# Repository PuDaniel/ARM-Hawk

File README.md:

The ARM-Hawk project consists of a custom designed radio controlled airplane equipped with a scratch built flight computer running custom software. The goal of the project is to develop a system to greatly enhance the flight characteristics of the airplane, as well as to protect its flight envelope.
This repository includes the following parts of the project:

- [ARM_Hawk.pdf](ARM_Hawk.pdf) This file contains a complete description of the project, including the derivation of a flight model and simulation framework, sensor calibration and state estimation algorithms, and the control laws for lateral stability augmentation and stall protection
- [Air_Data_Sensor_Unit](Air_Data_Sensor_Unit) This directory contains information for building and calibrating the custom developed Air Data Probe
- [Airframe](Airframe) This directory contains some information about the airplane used
- [Electronics](Electronics) This directory contains plans for some electronic circuits (RPM sensor, servo switch)
- [Flight_Computer](Flight_Computer) This directory contains the C++ code for the flight software
- [IMU](IMU) This directory contains information for building and calibrating the custom developed Inertial Measurement Unit, as well as a model of the state estimation algorithm

Visit the project's YouTube channel to see some videos of the system in action:
[https://m.youtube.com/channel/UCTHfZXQw1zonnjaXaEWrNzA](https://m.youtube.com/channel/UCTHfZXQw1zonnjaXaEWrNzA)

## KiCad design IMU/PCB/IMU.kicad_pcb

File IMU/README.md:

# IMU

This directory contains all plans to build and calibrate the ARM-Hawk custom designed IMU. It consits of an *NXP FXAS21002* gyroscope and an *NXP FXOS8700* accelerometer/magnetometer. A CNC-machined baseplate provides an exact reference for calibration and mounting in the plane. A 3D-printed case protects the sensor ICs form high-current cables (magnetic fields).

- [Calibration_accelerometer](Calibration_accelerometer) contains a Matlab script to calibrate the accelerometer (a sample dataset and result is also included)
- [Calibration_gyro](Calibration_gyro) contains a Matlab script to calibrate the gyroscope (a sample dataset and result is also included)
- [Calibration_magnetometer](Calibration_magnetometer) contains two Matlab scripts to calibrate the magnetometer for the static case and the dynamic case with the motor running (a sample dataset and result is also included)
- [CAM](CAM) contains the g-code files needed for milling the baseplate (floor), the spacer and the interface PCB, as well as an STL file for 3D-printing the case
- [Jig](Jig) contains a g-code file to mill an alignment jig needed for calibration from an 1.5mm glassfibre plate
- [PCB](PCB) contains the KiCad project of the interface circuit and the PCB's gerber files
- [Simulation](Simulation) contains a *Simulink* model of the state estimation algorithm, which is performed from the flight computer in real time (a sample dataset recorded during a test flight is included)

CAD drawing with dimensions and rendering of the case:

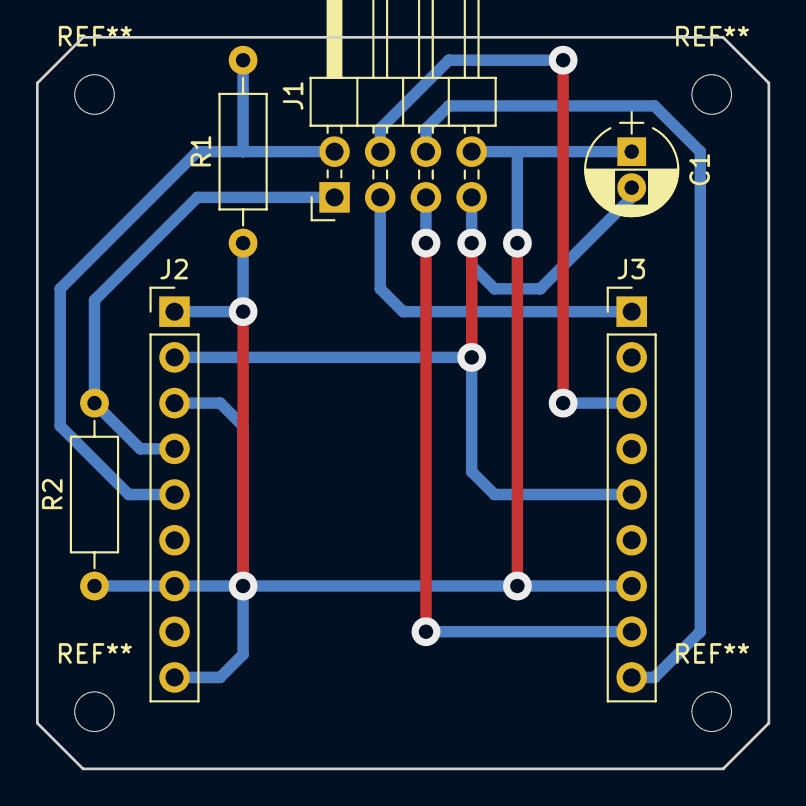
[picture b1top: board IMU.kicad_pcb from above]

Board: 2 copper layers, 40.6 x 40.6 mm, 6 parts (0 on the bottom side), 8 nets.

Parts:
C1: 1u; CP_Radial_D5.0mm_P2.00mm
J1: ARM_HAWK_CONN; Pin_Header_Angled_2x04_Pitch2.54mm
J2, J3: AGM01; Pin_Header_Straight_1x09_Pitch2.54mm
R1, R2: 1k5; R_Axial_DIN0207_L6.3mm_D2.5mm_P10.16mm_Horizontal

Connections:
GND: C1.2, J1.7, J2.2, J3.5
INT1_8700: J1.3, J3.1
INT1_21002: J1.5, J3.8
INT2_8700: J1.4, J3.3
INT2_21002: J1.6, J3.9
RST_21002: C1.1, J1.8, J2.1, J2.3, J2.7, J2.9, J3.7, R1.1, R2.1
SCL: J1.1, J2.4, R2.2
SDA: J1.2, J2.5, R1.2

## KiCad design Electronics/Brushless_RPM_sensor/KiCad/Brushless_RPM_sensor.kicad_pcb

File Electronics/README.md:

# Electronics

This directory contains all custom developed circuits used in the ARM-Hawk project.

### Brushless RPM sensor

This sensor is connected to two of the three BLDC motor's phases. It outputs a square wave with a frequency equal to that of the electric field's frequency.

- [Brushless_RPM_sensor/CAM](Brushless_RPM_sensor/CAM) contains g-code files for milling the PCB
- [Brushless_RPM_sensor/KiCad](Brushless_RPM_sensor/KiCad) contains the KiCAD project, as well as the PCB's gerber files

### Servoswitch

The servoswitch multiplexes the servo PWM signals coming either form the flight computer or the RC receiver. A PWM channel from the RC receiver can switch all four channel outputs between these two input sources. An ATtiny13 microcontroller executes the task of switching. Many failsafe features are included in the design.

- [Servoswitch/Code](Servoswitch/Code) contains the C program for the microcontroller
- [Servoswitch/KiCad](Servoswitch/KiCad) contains the KiCAD project (only schematic)

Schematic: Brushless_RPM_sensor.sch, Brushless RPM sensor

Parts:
C1: 100n; C_1206_HandSoldering
J1: PHASE A; SolderWirePad_single_1-2mmDrill
J2: PHASE B; SolderWirePad_single_1-2mmDrill
J3: JR Connector; Pin_Header_Angled_1x03_Pitch2.54mm
R1: 10k/22k; R_Axial_DIN0207_L6.3mm_D2.5mm_P10.16mm_Horizontal
R2, R3, R4: 470; R_1206_HandSoldering
R5: 220; R_1206_HandSoldering
R6, R7, R9: 1k; R_1206_HandSoldering
R8: 10k; R_1206_HandSoldering
U1, U2: PC817; DIP-4_W7.62mm
U3: MCP6002-xP; DIP-8_W7.62mm

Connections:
+5V: J3.3, R2.1, R6.1, U1.4, U3.8 (V+)
GND: C1.2, J3.2, R3.2, R7.2, U2.3, U3.4 (V-)
unnamed: C1.1, R4.1, U3.3 (+)
unnamed: J1.1, R1.1
unnamed: J2.1, U1.2, U2.1
unnamed: R1.2, U1.1, U2.2
unnamed: R2.2, R3.1, R4.2, U1.3, U2.4
unnamed: R5.1, U3.1, U3.2 (-)
unnamed: R5.2, R8.2, U3.5 (+)
unnamed: R6.2, R7.1, U3.6 (-)
unnamed: R8.1, R9.1, U3.7
RPM: J3.1, R9.2

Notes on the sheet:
R1 = 10k …2s-6s R1 = 22k …7s-14s

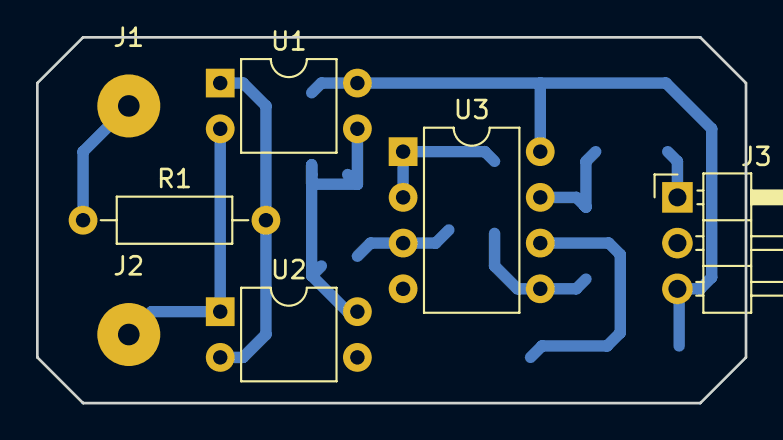
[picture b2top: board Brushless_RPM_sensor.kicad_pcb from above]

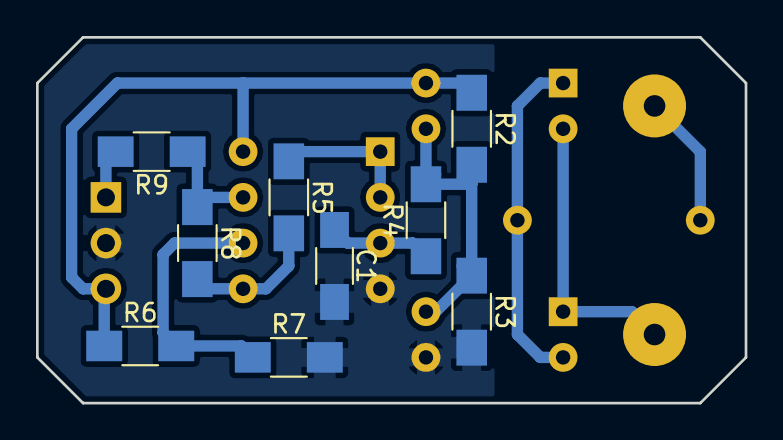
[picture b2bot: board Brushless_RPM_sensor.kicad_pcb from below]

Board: 2 copper layers, 39.4 x 20.3 mm, 16 parts (9 on the bottom side), 12 nets.

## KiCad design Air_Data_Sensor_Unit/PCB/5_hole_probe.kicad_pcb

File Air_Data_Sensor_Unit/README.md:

# Air Data Sensor Unit

This directory contains all plans to build the mechanical and electronical assembly of the Air Data Sensor Unit, as well as supporting files for obtaining calibrated measurements.

- [CAM](CAM) contains the g-code files for milling the two aluminum pieces (base and tip), the glassfibre mount, and the PCB, as well as STL files for the housing (3D-printed with PLA)
- [CFD](CFD) contains the pressure coefficient at the probe's tip computed with *ANSYS*, as well as the calibration curve for the static pressure port
- [Matlab](Matlab) contains three scripts for calculating the realtions between differential pressures and the flow parameters (airspeed, alpha, beta), as well as a set of precomputed characteristics:
  - *alpha_beta_algorithm.m* Computes alpha, beta and airspeed from the three measured differential pressures iteratively
  - *characterisitic.m* Computes and plots characteristic curves of alpha and beta for fixed total pressures
  - *lookup_table.m* Computes a lookup table to be used in real time from the flight computer (result of script is found in [AirDataComputer_data.cpp](/Flight_Computer/Main/sensors/AirDataComputer_data.cpp))
- [PCB](PCB) contains the KiCad project of the sensor circuit, along with the gerber files of the PCB

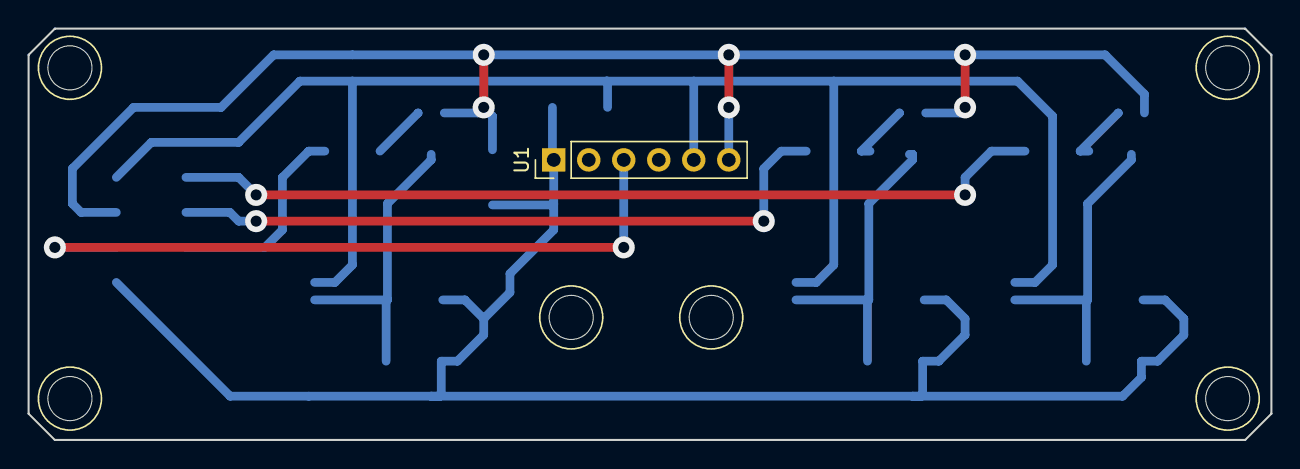
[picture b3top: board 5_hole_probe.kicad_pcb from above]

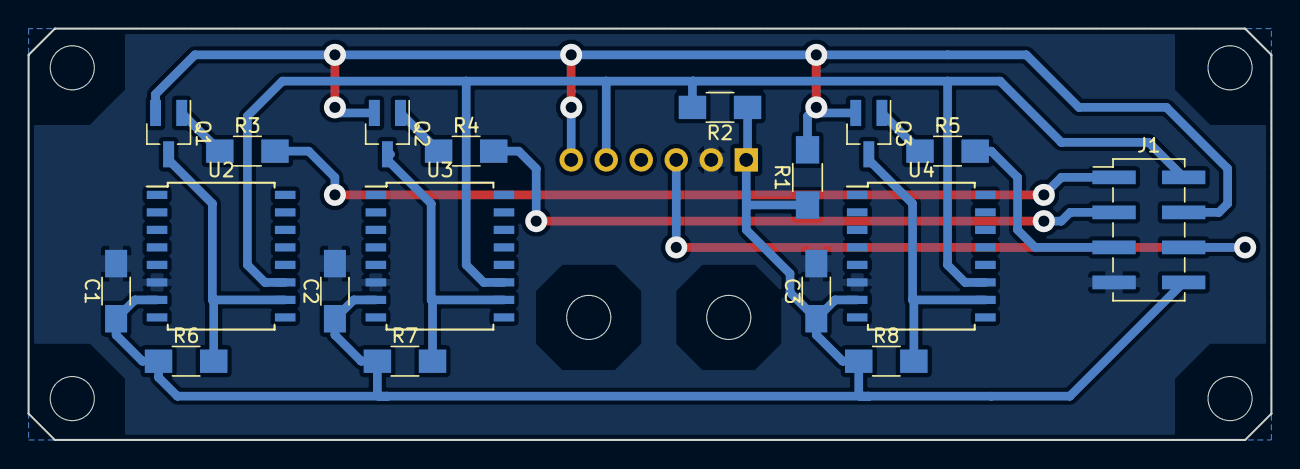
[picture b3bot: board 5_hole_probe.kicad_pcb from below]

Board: 2 copper layers, 90.2 x 29.8 mm, 19 parts (18 on the bottom side), 14 nets.

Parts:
C1, C2, C3: 100n; C_1206_HandSoldering
J1: ARM_HAWK_CONN; Pin_Header_Straight_2x04_Pitch2.54mm_SMD
Q1, Q2, Q3: MMBT2222; SOT-23_Handsoldering
R1, R2, R6, R7, R8: 10k; R_1206_HandSoldering
R3, R4, R5: 1k; R_1206_HandSoldering
U1: BMP085_Breakout; Pin_Header_Straight_1x06_Pitch2.54mm
U2: SM9541-020C-D-C-3-S; SOIC-16W_7.5x10.3mm_Pitch1.27mm
U3, U4: SM9541-010C-D-C-3-S; SOIC-16W_7.5x10.3mm_Pitch1.27mm

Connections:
+3V3: C1.1, C2.1, C3.1, J1.8, R1.1, R2.1, R6.1, R7.1, R8.1, U1.1, U2.7, U3.7, U4.7
EN1: J1.1, R3.2
EN2: J1.3, R4.2
EN3: J1.5, R5.2
EOC: J1.6, U1.3
GND: C1.2, C2.2, C3.2, J1.7, U1.2, U2.6, U3.6, U4.6
unnamed: Q1.1, R3.1
unnamed: Q2.1, R4.1
unnamed: Q3.1, R5.1
SCL: J1.2, R2.2, U1.5, U2.11, U3.11, U4.11
SDA: J1.4, Q1.2, Q2.2, Q3.2, R1.2, U1.6
SDA1: Q1.3, R6.2, U2.10
SDA2: Q2.3, R7.2, U3.10
SDA3: Q3.3, R8.2, U4.10

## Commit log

2018-12-13 Add existing file
2018-12-15 Corrections in ARM-Hawk.pdf
